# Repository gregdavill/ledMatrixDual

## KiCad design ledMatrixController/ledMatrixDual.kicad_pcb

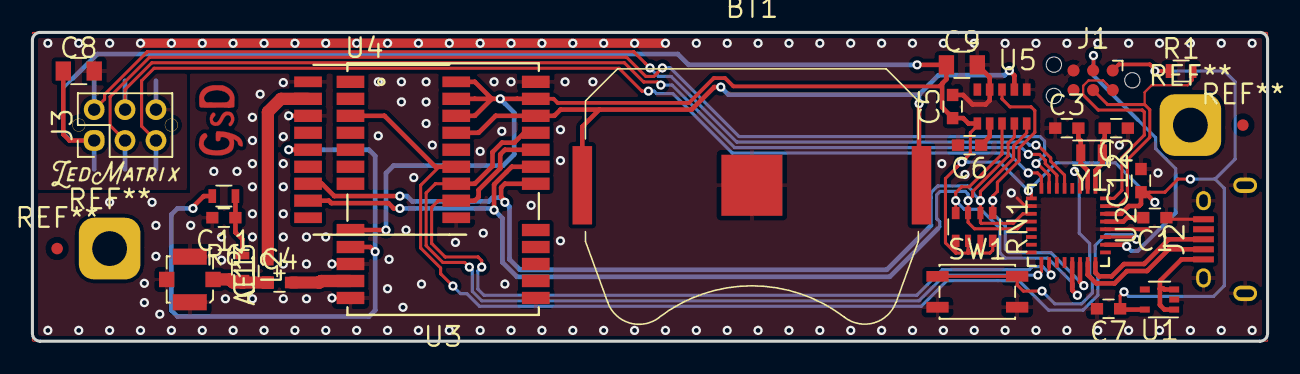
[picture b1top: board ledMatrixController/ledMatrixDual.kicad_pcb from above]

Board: 2 copper layers, 80.0 x 20.0 mm, 28 parts (0 on the bottom side), 30 nets.

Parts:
AE1: IPX; Molex_Microcoaxial_RF
BT1: Battery_Cell; Keystone_3034_1x20mm-CoinCell
C1, C5, C7, C12: 100n; C_0603
C2, C3: 9pF; C_0603
C4, C11, C13: 10n; C_0603
C6: 47pF; C_0603
C8, C9: 10uF; C_0805
J1: TC2030-CTX; Tag-Connect_TC2030-IDC-NL
J2: USB_OTG; USB_Micro-B
J3: Conn_02x03_Odd_Even; Pin_Header_Straight_2x03_Pitch2.00mm
L2: 47nH; L_0603
R1: 1K; R_0603
R6: 10R; R_0603
RN1: 4.7K; R_Array_Convex_4x0603
SW1: TACT_SW; SW_SPST_EVQP2
U1: MIC5365; SOT-353_SC-70-5
U2: SAMD21E18A; QFN-32-1EP_5x5mm_Pitch0.5mm
U3: NEO_M8; NEO-M8
U4: MAX_M8Q; MAX_M8
U5: AB-RTCMC; 10-DFN
Y1: 32.768kHz; Crystal_SMD_2012-2pin_2.0x1.2mm

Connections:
+3V3: C5.1, C7.1, C8.1, C9.1, C12.1, J1.1, J3.1, R1.1, RN1.5, RN1.6, RN1.7, RN1.8, U1.5, U2.9, U2.30, U3.8, U3.23, U4.7, U4.8, U4.9, U5.1
ANT_PWR: R6.2, U3.9, U4.14
BUTTON: SW1.1, U2.3
CTX_RST: J1.3, U2.26
CTX_SWCLK: J1.4, R1.2, U2.31
CTX_SWDIO: J1.2, U2.32
DIS_CLK: J3.4, U2.6
DIS_LATCH: J3.3, U2.7
DIS_OE: J3.5, U2.8
DIS_SER: J3.2, U2.5
GND: AE1.2, BT1.2, C1.1, C2.1, C3.1, C5.2, C6.2, C7.2, C8.2, C9.2, C11.2, C12.2, J1.5, J2.5, J2.6, J3.6, SW1.2, U1.2, U2.10, U2.28, U3.10, U3.12, U3.13, U3.24, U4.1, U4.10, U4.12, U5.6, U5.9
GPS_PPS: U2.27, U3.3, U4.4
GPS_RX: U2.18, U3.20, U4.2
GPS_TX: U2.17, U3.21, U4.3
I2C_SCL: RN1.3, U2.12, U3.19, U4.17, U5.4
I2C_SDA: RN1.2, U2.11, U3.18, U4.16, U5.5
unnamed: AE1.1, C4.1, C13.1, L2.2
unnamed: C1.2, U2.29
unnamed: C2.2, U2.1, Y1.1
unnamed: C3.2, U2.2, Y1.2
unnamed: C4.2, U3.11
unnamed: C6.1, U5.2
unnamed: C11.1, L2.1, R6.1
unnamed: C13.2, U4.11
RTC_INT1: RN1.4, U2.21, U5.3
RTC_INT2: RN1.1, U2.22, U5.8
USB_DM: J2.2, U2.23
USB_DP: J2.3, U2.24
USB_VBUS: J2.1, U1.1, U1.3
V_BCKP: BT1.1, U3.22, U4.6, U5.7

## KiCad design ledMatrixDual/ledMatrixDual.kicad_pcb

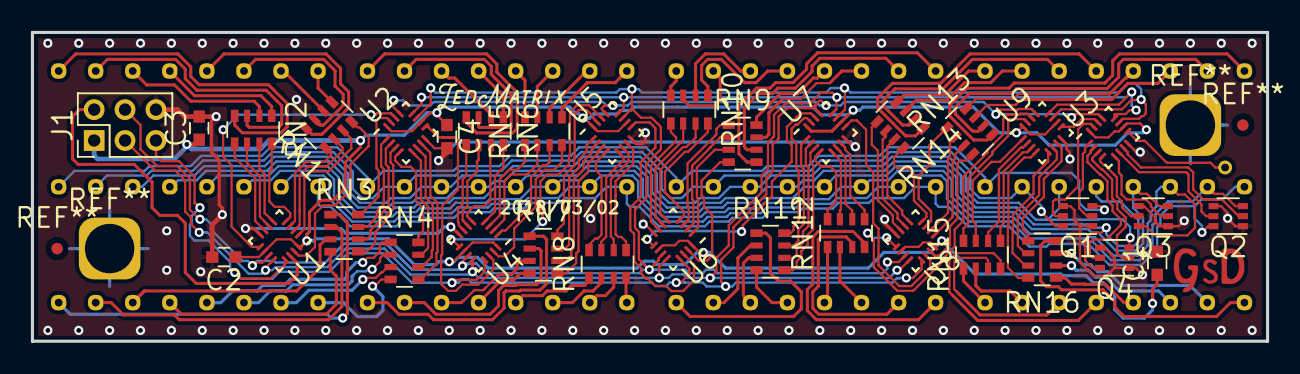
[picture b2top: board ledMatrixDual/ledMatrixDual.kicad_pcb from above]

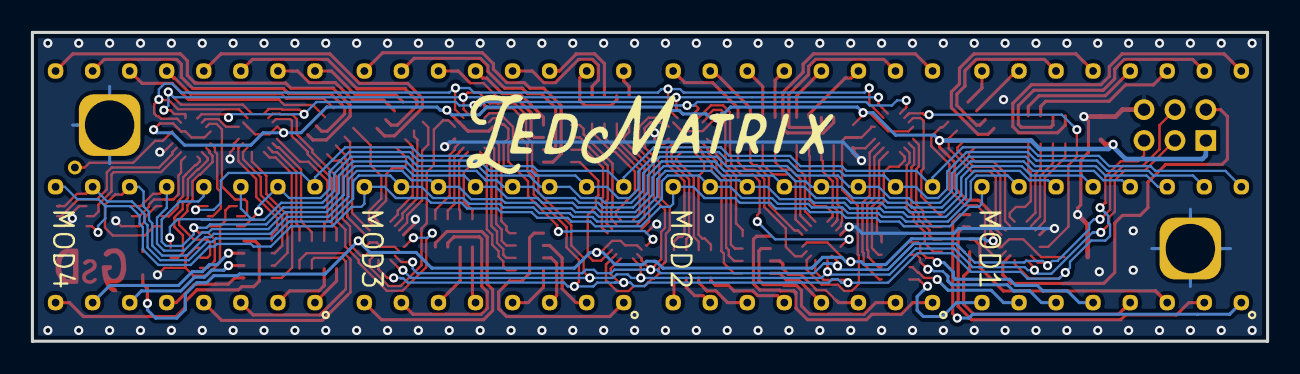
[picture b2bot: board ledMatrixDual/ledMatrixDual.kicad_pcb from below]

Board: 2 copper layers, 80.0 x 20.0 mm, 38 parts (4 on the bottom side), 158 nets.

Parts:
C1, C2, C3, C4: 100n; C_0603
J1: Conn_02x03_Odd_Even; Pin_Header_Straight_2x03_Pitch2.00mm
MOD1, MOD2, MOD3, MOD4: KEM-7088
Q1, Q2, Q3, Q4: DMN53D0LDW; SOT-363_SC-70-6
RN1, RN2, RN3, RN4, RN5, RN6, RN7, RN8, RN9, RN10, RN11, RN12, RN13, RN14, RN15, RN16: R_Pack04; R_Array_Convex_4x0603
U1, U2, U3, U4, U5, U6, U7, U8, U9: SN74HC595B; UQFN-16-1EP_3x3mm_Pitch0.5mm

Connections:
+3V3: C1.1, C2.1, C3.1, C4.1, J1.1, U1.10, U1.16, U2.10, U2.16, U3.10, U3.16, U4.10, U4.16, U5.10, U5.16, U6.10, U6.16, U7.10, U7.16, U8.10, U8.16, U9.10, U9.16
/ledCommon/SIN: U3.14, U9.9
/ledModule_1/SIN: U2.9, U4.14
/ledModule_2/SIN: U5.9, U6.14
/ledModule_3/SIN: U7.9, U8.14
CLK: J1.4, U1.11, U2.11, U3.11, U4.11, U5.11, U6.11, U7.11, U8.11, U9.11
GND: C1.2, C2.2, C3.2, C4.2, J1.6, Q1.1, Q1.4, Q2.1, Q2.4, Q3.1, Q3.4, Q4.1, Q4.4, U1.8, U2.8, U3.8, U4.8, U5.8, U6.8, U7.8, U8.8, U9.8
LED_COM0: MOD1.16, MOD2.16, MOD3.16, MOD4.16, Q2.6
LED_COM1: MOD1.15, MOD2.15, MOD3.15, MOD4.15, Q2.3
LED_COM2: MOD1.14, MOD2.14, MOD3.14, MOD4.14, Q3.6
LED_COM3: MOD1.13, MOD2.13, MOD3.13, MOD4.13, Q3.3
LED_COM4: MOD1.12, MOD2.12, MOD3.12, MOD4.12, Q4.6
LED_COM5: MOD1.11, MOD2.11, MOD3.11, MOD4.11, Q4.3
LED_COM6: MOD1.10, MOD2.10, MOD3.10, MOD4.10, Q1.6
LED_COM7: MOD1.9, MOD2.9, MOD3.9, MOD4.9, Q1.3
unnamed: MOD1.1, RN3.1
unnamed: MOD1.2, RN3.2
unnamed: MOD1.3, RN3.3
unnamed: MOD1.4, RN3.4
unnamed: MOD1.5, RN4.1
unnamed: MOD1.6, RN4.2
unnamed: MOD1.7, RN4.3
unnamed: MOD1.8, RN4.4
unnamed: MOD1.17, RN2.4
unnamed: MOD1.18, RN2.3
unnamed: MOD1.19, RN2.2
unnamed: MOD1.20, RN2.1
unnamed: MOD1.21, RN1.8
unnamed: MOD1.22, RN1.7
unnamed: MOD1.23, RN1.6
unnamed: MOD1.24, RN1.5
unnamed: MOD2.1, RN7.1
unnamed: MOD2.2, RN7.2
unnamed: MOD2.3, RN7.3
unnamed: MOD2.4, RN7.4
unnamed: MOD2.5, RN8.1
unnamed: MOD2.6, RN8.2
unnamed: MOD2.7, RN8.3
unnamed: MOD2.8, RN8.4
unnamed: MOD2.17, RN6.4
unnamed: MOD2.18, RN6.3
unnamed: MOD2.19, RN6.2
unnamed: MOD2.20, RN6.1
unnamed: MOD2.21, RN5.8
unnamed: MOD2.22, RN5.7
unnamed: MOD2.23, RN5.6
unnamed: MOD2.24, RN5.5
unnamed: MOD3.1, RN11.1
unnamed: MOD3.2, RN11.2
unnamed: MOD3.3, RN11.3
unnamed: MOD3.4, RN11.4
unnamed: MOD3.5, RN12.1
unnamed: MOD3.6, RN12.2
unnamed: MOD3.7, RN12.3
unnamed: MOD3.8, RN12.4
unnamed: MOD3.17, RN10.4
unnamed: MOD3.18, RN10.3
unnamed: MOD3.19, RN10.2
unnamed: MOD3.20, RN10.1
unnamed: MOD3.21, RN9.8
unnamed: MOD3.22, RN9.7
unnamed: MOD3.23, RN9.6
unnamed: MOD3.24, RN9.5
unnamed: MOD4.1, RN15.1
unnamed: MOD4.2, RN15.2
unnamed: MOD4.3, RN15.3
unnamed: MOD4.4, RN15.4
unnamed: MOD4.5, RN16.1
unnamed: MOD4.6, RN16.2
unnamed: MOD4.7, RN16.3
unnamed: MOD4.8, RN16.4
unnamed: MOD4.17, RN14.4
unnamed: MOD4.18, RN14.3
unnamed: MOD4.19, RN14.2
unnamed: MOD4.20, RN14.1
unnamed: MOD4.21, RN13.8
unnamed: MOD4.22, RN13.7
unnamed: MOD4.23, RN13.6
unnamed: MOD4.24, RN13.5
unnamed: Q1.2, U3.1
unnamed: Q1.5, U3.15
unnamed: Q2.2, U3.7
unnamed: Q2.5, U3.6
unnamed: Q3.2, U3.5
unnamed: Q3.5, U3.4
unnamed: Q4.2, U3.3
unnamed: Q4.5, U3.2
unnamed: RN1.1, U1.3
unnamed: RN1.2, U1.2
unnamed: RN1.3, U1.1
unnamed: RN1.4, U1.15
unnamed: RN2.5, U1.7
unnamed: RN2.6, U1.6
unnamed: RN2.7, U1.5
unnamed: RN2.8, U1.4
unnamed: RN3.5, U2.3
unnamed: RN3.6, U2.2
unnamed: RN3.7, U2.1
unnamed: RN3.8, U2.15
unnamed: RN4.5, U2.7
unnamed: RN4.6, U2.6
unnamed: RN4.7, U2.5
unnamed: RN4.8, U2.4
unnamed: RN5.1, U4.3
unnamed: RN5.2, U4.2
unnamed: RN5.3, U4.1
unnamed: RN5.4, U4.15
unnamed: RN6.5, U4.7
unnamed: RN6.6, U4.6
unnamed: RN6.7, U4.5
unnamed: RN6.8, U4.4
unnamed: RN7.5, U5.3
unnamed: RN7.6, U5.2
unnamed: RN7.7, U5.1
unnamed: RN7.8, U5.15
unnamed: RN8.5, U5.7
unnamed: RN8.6, U5.6
unnamed: RN8.7, U5.5
unnamed: RN8.8, U5.4
unnamed: RN9.1, U6.3
unnamed: RN9.2, U6.2
unnamed: RN9.3, U6.1
unnamed: RN9.4, U6.15
unnamed: RN10.5, U6.7
unnamed: RN10.6, U6.6
unnamed: RN10.7, U6.5
unnamed: RN10.8, U6.4
unnamed: RN11.5, U7.3
unnamed: RN11.6, U7.2
unnamed: RN11.7, U7.1
unnamed: RN11.8, U7.15
unnamed: RN12.5, U7.7
unnamed: RN12.6, U7.6
unnamed: RN12.7, U7.5
unnamed: RN12.8, U7.4
unnamed: RN13.1, U8.3
unnamed: RN13.2, U8.2
unnamed: RN13.3, U8.1
unnamed: RN13.4, U8.15
unnamed: RN14.5, U8.7
unnamed: RN14.6, U8.6
unnamed: RN14.7, U8.5
unnamed: RN14.8, U8.4
unnamed: RN15.5, U9.3
unnamed: RN15.6, U9.2
unnamed: RN15.7, U9.1
unnamed: RN15.8, U9.15
unnamed: RN16.5, U9.7
unnamed: RN16.6, U9.6
unnamed: RN16.7, U9.5
unnamed: RN16.8, U9.4
unnamed: U1.9, U2.14
unnamed: U4.9, U5.14
unnamed: U6.9, U7.14
unnamed: U8.9, U9.14
OE: J1.5, U1.13, U2.13, U3.13, U4.13, U5.13, U6.13, U7.13, U8.13, U9.13
RCLK: J1.3, U1.12, U2.12, U3.12, U4.12, U5.12, U6.12, U7.12, U8.12, U9.12
SER: J1.2, U1.14
